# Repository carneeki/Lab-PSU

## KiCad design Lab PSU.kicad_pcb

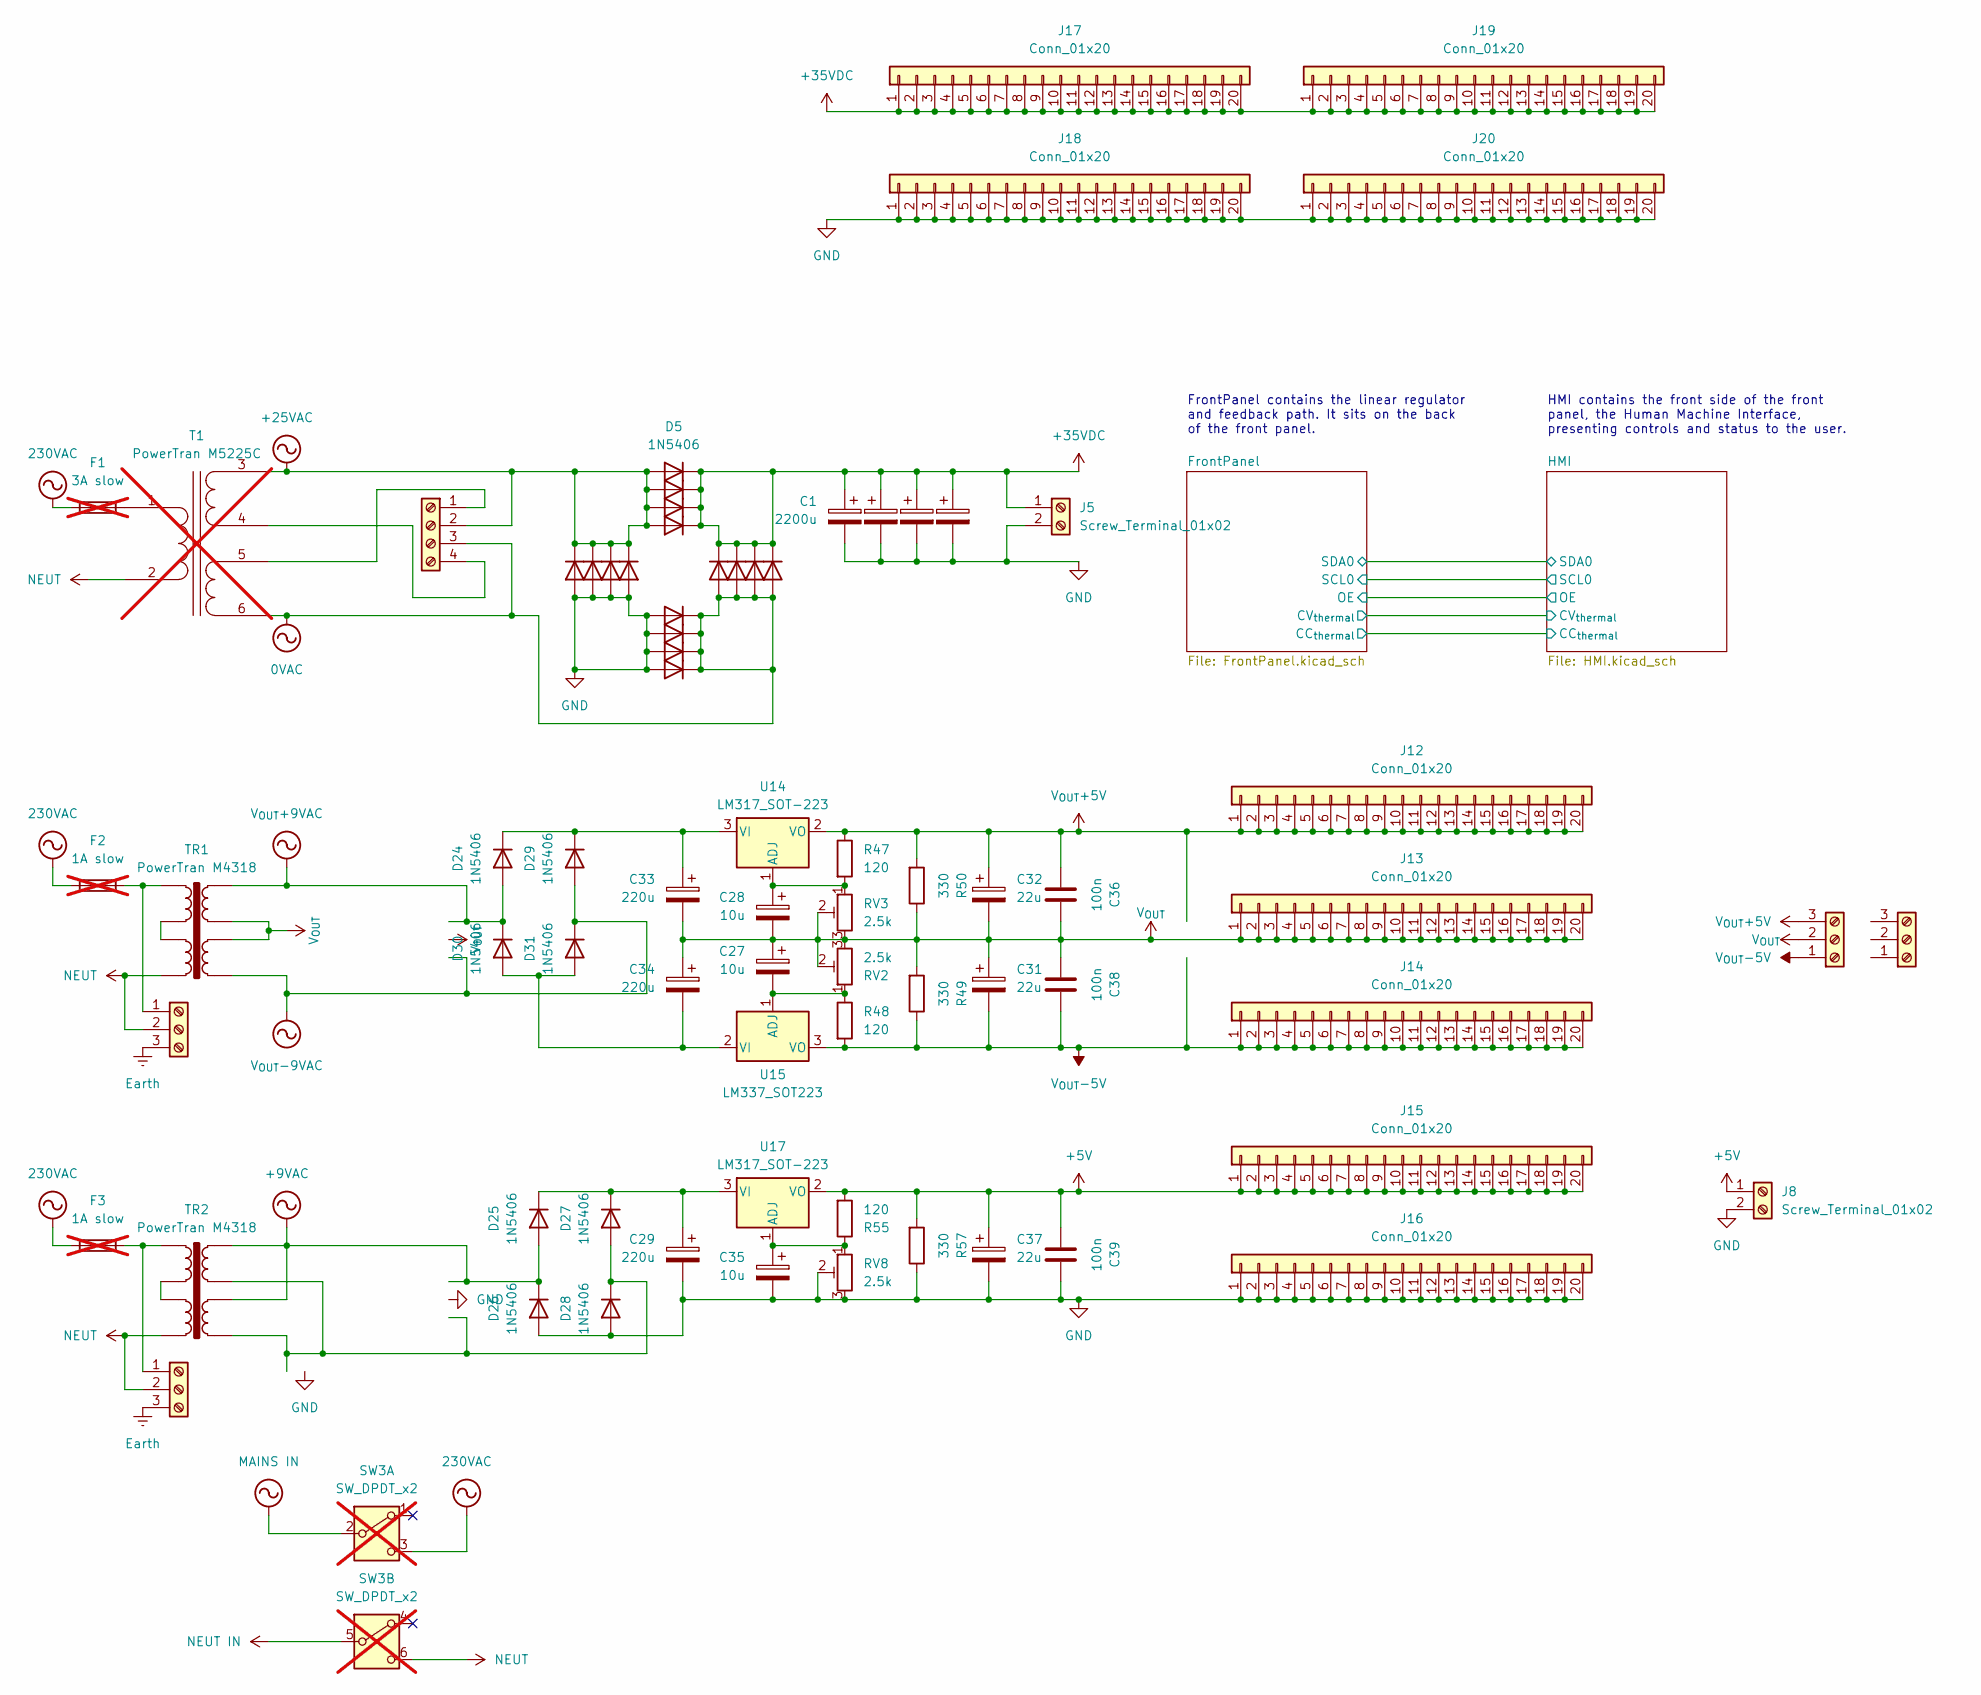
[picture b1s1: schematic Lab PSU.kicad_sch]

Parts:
C1, C2, C3, C4: 2200u; CP_Radial_D18.0mm_P7.50mm
C27, C28, C35: 10u; CP_Radial_D5.0mm_P2.00mm
C29, C33, C34: 220u; CP_Radial_D10.0mm_P5.00mm_P7.50mm
C31, C32, C37: 22u; CP_Radial_D6.3mm_P2.50mm
C36, C38, C39: 100n; C_1210_3225Metric_Pad1.33x2.70mm_HandSolder
D1, D2, D3, D4, D5, D6, D7, D8, D9, D10, D11, D12, D13, D14, D15, D16, D24, D25, D26, D27, D28, D29, D30, D31: 1N5406; D_DO-201AD_P15.24mm_Horizontal
F1: 3A slow; not fitted
F2, F3: 1A slow; not fitted
J1: Screw_Terminal_01x04; TerminalBlock_4Ucon_1x04_P3.50mm_Vertical
J4, J6, J7, J11: Screw_Terminal_01x03; TerminalBlock_4Ucon_1x03_P3.50mm_Vertical
J5, J8: Screw_Terminal_01x02; TerminalBlock_4Ucon_1x02_P3.50mm_Horizontal
J12, J13, J14, J15, J16, J17, J18: Conn_01x20; PinSocket_1x20_P2.54mm_Vertical
J19, J20: Conn_01x20; PinHeader_1x20_P2.54mm_Vertical
R47, R48, R55: 120; R_1210_3225Metric_Pad1.30x2.65mm_HandSolder
R49, R50, R57: 330; R_1210_3225Metric_Pad1.30x2.65mm_HandSolder
RV2, RV3, RV8: 2.5k; Potentiometer_Bourns_3299W_Vertical
SW3: SW_DPDT_x2; not fitted
T1: PowerTran M5225C; not fitted
TR1, TR2: PowerTran M4318; Transformer 53x53
U14, U17: LM317_SOT-223; SOT-223-3_TabPin2
U15: LM337_SOT223; SOT-223-3_TabPin2

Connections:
0VAC: D9.2 (A), D10.2 (A), D11.2 (A), D12.2 (A), D13.1 (K), D14.1 (K), D15.1 (K), D16.1 (K), J1.3, T1.6 (SD)
+5V: C37.1, C39.2, J8.1, J15.1, J15.2, J15.3, J15.4, J15.5, J15.6, J15.7, J15.8, J15.9, J15.10, J15.11, J15.12, J15.13, J15.14, J15.15, J15.16, J15.17, J15.18, J15.19, J15.20, R55.2, R57.2, U17.2 (VO); also elsewhere on the board
+9VAC: D25.2 (A), D26.1 (K), TR2.6, TR2.8
+25VAC: D1.1 (K), D2.1 (K), D3.1 (K), D4.1 (K), D5.2 (A), D6.2 (A), D7.2 (A), D8.2 (A), J1.2, T1.3 (SA)
+35VDC: C1.1, C2.1, C3.1, C4.1, D5.1 (K), D6.1 (K), D7.1 (K), D8.1 (K), D9.1 (K), D10.1 (K), D11.1 (K), D12.1 (K), J5.1, J17.1, J17.2, J17.3, J17.4, J17.5, J17.6, J17.7, J17.8, J17.9, J17.10, J17.11, J17.12, J17.13, J17.14, J17.15, J17.16, J17.17, J17.18, J17.19, J17.20, J19.1, J19.2, J19.3, J19.4, J19.5, J19.6, J19.7, J19.8, J19.9, J19.10, J19.11, J19.12, J19.13, J19.14, J19.15, J19.16, J19.17, J19.18, J19.19, J19.20; also elsewhere on the board
Earth: J6.3, J7.3
GND: C1.2, C2.2, C3.2, C4.2, C29.2, C35.2, C37.2, C39.1, D1.2 (A), D2.2 (A), D3.2 (A), D4.2 (A), D13.2 (A), D14.2 (A), D15.2 (A), D16.2 (A), D26.2 (A), D28.2 (A), J5.2, J8.2, J16.1, J16.2, J16.3, J16.4, J16.5, J16.6, J16.7, J16.8, J16.9, J16.10, J16.11, J16.12, J16.13, J16.14, J16.15, J16.16, J16.17, J16.18, J16.19, J16.20, J18.1, J18.2, J18.3, J18.4, J18.5, J18.6, J18.7, J18.8, J18.9, J18.10, J18.11, J18.12, J18.13, J18.14, J18.15, J18.16, J18.17, J18.18, J18.19, J18.20, J20.1, J20.2, J20.3, J20.4, J20.5, J20.6, J20.7, J20.8, J20.9, J20.10, J20.11, J20.12, J20.13, J20.14, J20.15, J20.16, J20.17, J20.18, J20.19, J20.20, R57.1, RV8.2, RV8.3; also elsewhere on the board
NEUT: J6.2, J7.2, SW3.6 (C), T1.2 (AB), TR1.4, TR2.4
unnamed: C33.1, D24.1 (K), D29.1 (K), U14.3 (VI)
unnamed: C29.1, D25.1 (K), D27.1 (K), U17.3 (VI)
unnamed: D27.2 (A), D28.1 (K), TR2.5, TR2.7
unnamed: C34.2, D30.2 (A), D31.2 (A), U15.2 (VI)
unnamed: F1.1, F2.1, F3.1, SW3.3 (C)
unnamed: F1.2, T1.1 (AA)
unnamed: J1.1, T1.5 (SC)
unnamed: J1.4, T1.4 (SB)
unnamed: F2.2, J6.1, TR1.1
unnamed: F3.2, J7.1, TR2.1
unnamed: TR1.2, TR1.3
unnamed: TR2.2, TR2.3
unnamed: C28.1, R47.2, RV3.1, U14.1 (ADJ)
unnamed: C27.2, R48.1, RV2.1, U15.1 (ADJ)
unnamed: C35.1, R55.1, RV8.1, U17.1 (ADJ)
V_{OUT}: C27.1, C28.2, C31.1, C32.2, C33.2, C34.1, C36.1, C38.1, J11.2, J13.1, J13.2, J13.3, J13.4, J13.5, J13.6, J13.7, J13.8, J13.9, J13.10, J13.11, J13.12, J13.13, J13.14, J13.15, J13.16, J13.17, J13.18, J13.19, J13.20, R49.2, R50.1, RV2.2, RV2.3, RV3.2, RV3.3, TR1.6, TR1.7; also elsewhere on the board
V_{OUT}+5V: C32.1, C36.2, J11.3, J12.1, J12.2, J12.3, J12.4, J12.5, J12.6, J12.7, J12.8, J12.9, J12.10, J12.11, J12.12, J12.13, J12.14, J12.15, J12.16, J12.17, J12.18, J12.19, J12.20, R47.1, R50.2, U14.2 (VO); also elsewhere on the board
V_{OUT}+9VAC: D24.2 (A), D30.1 (K), TR1.8
V_{OUT}-5V: C31.2, C38.2, J11.1, J14.1, J14.2, J14.3, J14.4, J14.5, J14.6, J14.7, J14.8, J14.9, J14.10, J14.11, J14.12, J14.13, J14.14, J14.15, J14.16, J14.17, J14.18, J14.19, J14.20, R48.2, R49.1, U15.3 (VO); also elsewhere on the board
V_{OUT}-9VAC: D29.2 (A), D31.1 (K), TR1.5

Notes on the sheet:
FrontPanel contains the linear regulator and feedback path. It sits on the back of the front panel.
HMI contains the front side of the front panel, the Human Machine Interface, presenting controls and status to the user.

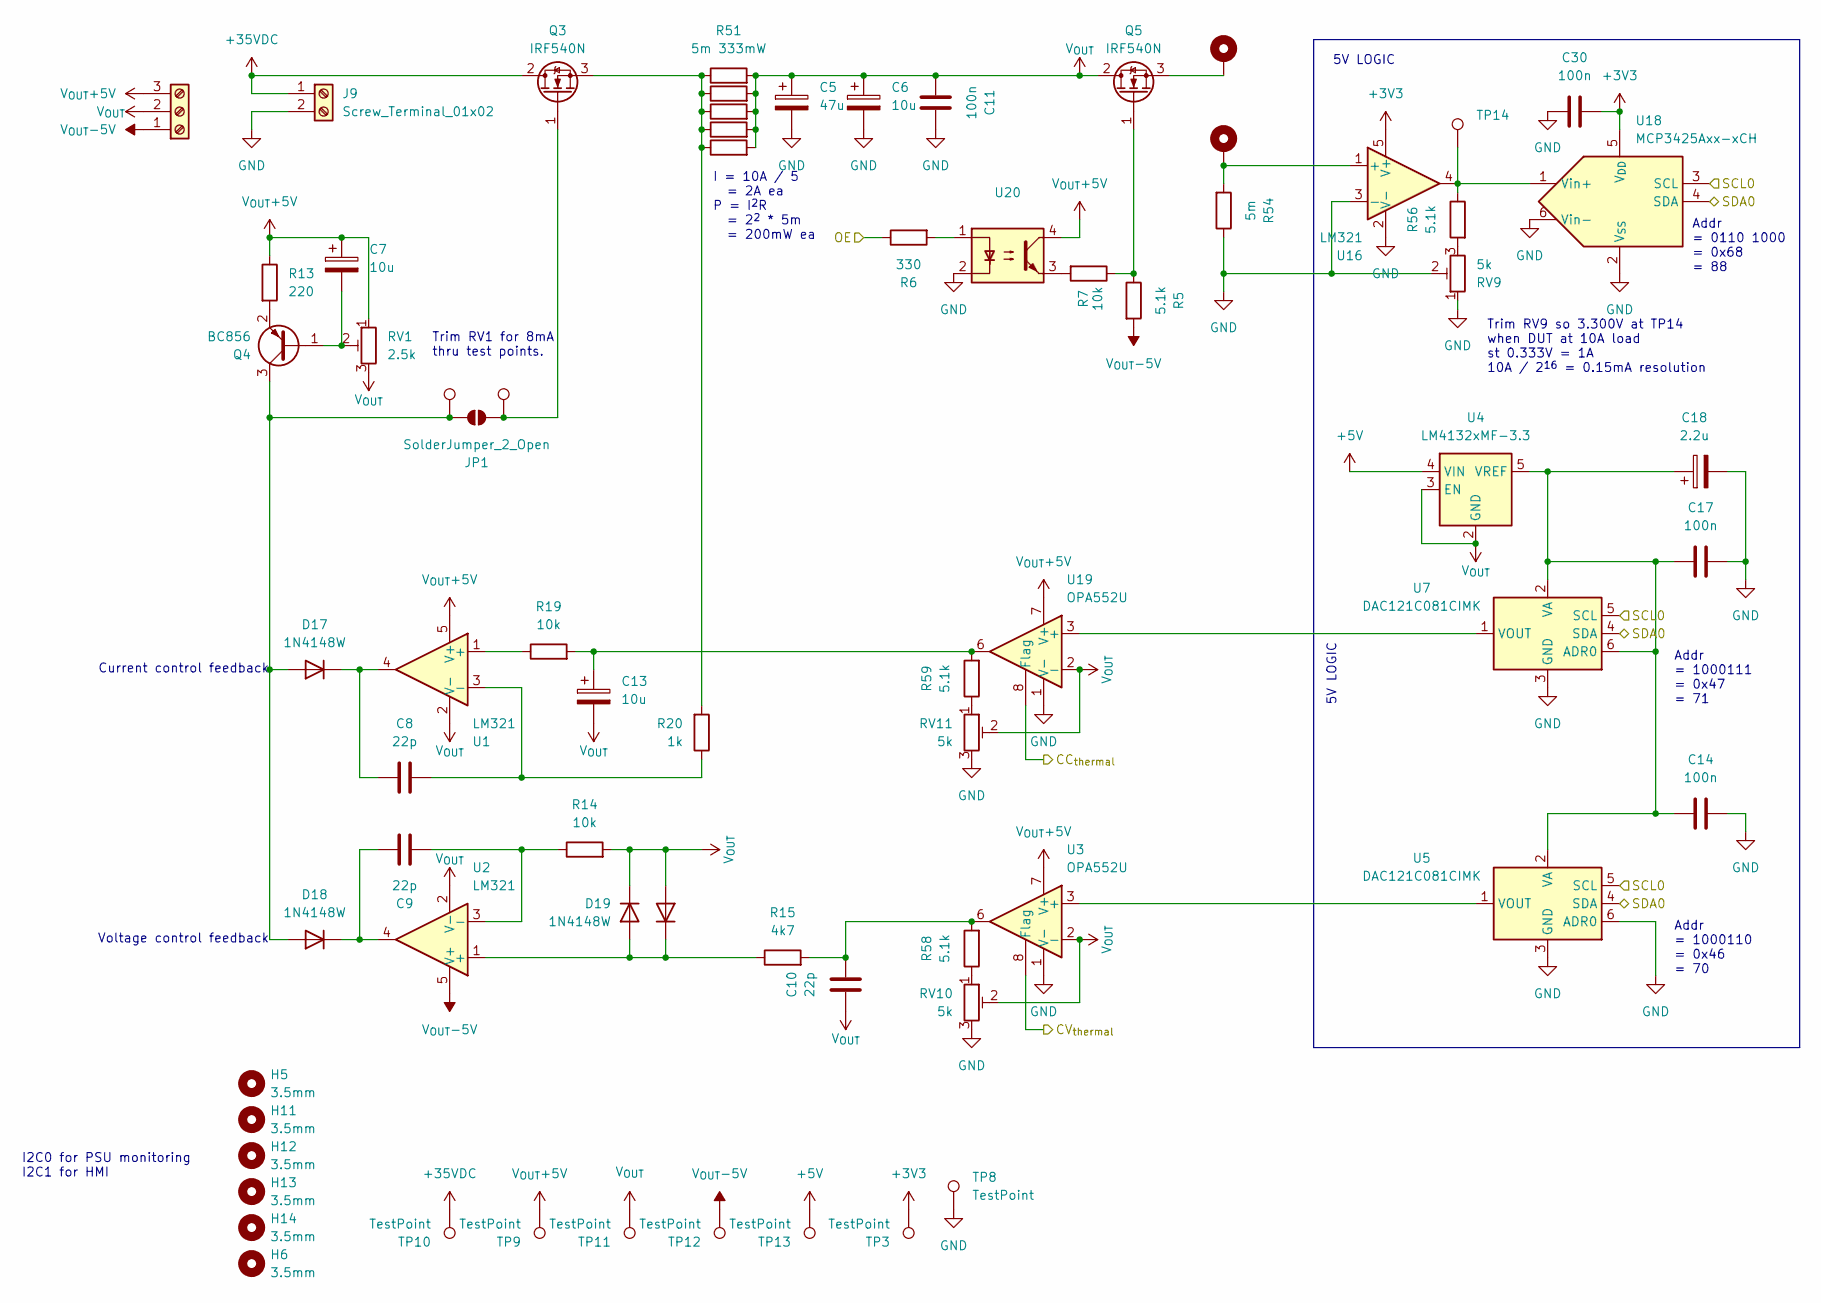
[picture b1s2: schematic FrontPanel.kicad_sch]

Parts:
C5: 47u; CP_Radial_D8.0mm_P3.50mm
C6, C7, C13: 10u; CP_Radial_D5.0mm_P2.00mm
C8, C9, C10: 22p; C_1210_3225Metric_Pad1.33x2.70mm_HandSolder
C11, C14, C17, C30: 100n; C_1210_3225Metric_Pad1.33x2.70mm_HandSolder
C18: 2.2u; CP_Radial_D5.0mm_P2.00mm
D17, D18, D19, D20: 1N4148W; D_SOD-123
H1, H2: MountingHole_Pad; MountingHole_4.3mm_M4_Pad_TopBottom
H5, H6, H11, H12, H13, H14: 3.5mm; MountingHole_3mm_Pad
J9: Screw_Terminal_01x02; TerminalBlock_4Ucon_1x02_P3.50mm_Horizontal
J10: Screw_Terminal_01x03; TerminalBlock_4Ucon_1x03_P3.50mm_Vertical
JP1: SolderJumper_2_Open; SolderJumper-2_P1.3mm_Open_TrianglePad1.0x1.5mm
Q3, Q5: IRF540N; TO-220-3_Vertical
Q4: BC856; SOT-23_Handsoldering
R1, R2, R3, R4, R54: 5m; R_0603_1608Metric_Pad0.98x0.95mm_HandSolder
R5, R56, R58, R59: 5.1k; R_1210_3225Metric_Pad1.30x2.65mm_HandSolder
R6: 330; R_1210_3225Metric_Pad1.30x2.65mm_HandSolder
R7, R14, R19: 10k; R_1210_3225Metric_Pad1.30x2.65mm_HandSolder
R13: 220; R_1210_3225Metric_Pad1.30x2.65mm_HandSolder
R15: 4k7; R_1210_3225Metric_Pad1.30x2.65mm_HandSolder
R20: 1k; R_1210_3225Metric_Pad1.30x2.65mm_HandSolder
R51: 5m 333mW; R_0603_1608Metric_Pad0.98x0.95mm_HandSolder
RV1: 2.5k; Potentiometer_Bourns_3299W_Vertical
RV9, RV10, RV11: 5k; Potentiometer_Bourns_3299W_Vertical
TP1, TP2: TestPoint; TestPoint_Keystone_5015_Micro_Mini
TP3, TP8, TP9, TP10, TP11, TP12, TP13, TP14: TestPoint; TestPoint_Keystone_5019_Miniature
U1, U2: LM321; SSOP-14_5.3x6.2mm_P0.65mm
U3, U19: OPA552U; SOIC-8_3.9x4.9mm_P1.27mm
U4: LM4132xMF-3.3; SOT-23-5
U5, U7: DAC121C081CIMK; SOT-23-6
U16: LM321; SOT-23-5_HandSoldering
U18: MCP3425Axx-xCH; SOT-23-6
U20: Optocoupler_DC_PhotoNPN_AKEC; DIP-4_W7.62mm_Socket_LongPads

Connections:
+3V3: C30.1, TP3.1 (1_1), U16.5 (V+), U18.5 (V_{DD}); also elsewhere on the board
+5V: TP13.1 (1_1), U4.4 (VIN); also elsewhere on the board
+35VDC: J9.1, Q3.2 (D), TP10.1 (1_1); also elsewhere on the board
/FrontPanel/CC_{thermal}: U19.8 (Flag); also elsewhere on the board
/FrontPanel/CV_{thermal}: U3.8 (Flag); also elsewhere on the board
/FrontPanel/OE: R6.1; also elsewhere on the board
/FrontPanel/SCL0: U5.5 (SCL), U7.5 (SCL), U18.3 (SCL); also elsewhere on the board
/FrontPanel/SDA0: U5.4 (SDA), U7.4 (SDA), U18.4 (SDA); also elsewhere on the board
GND: C5.2, C6.2, C11.2, C14.2, C17.2, C18.2, C30.2, J9.2, R54.1, RV9.1, RV9.2, RV10.3, RV11.3, TP8.1 (1_1), U3.1 (V-), U3.4 (V-), U3.5 (V-), U5.3 (GND), U5.6 (ADR0), U7.3 (GND), U16.2 (V-), U16.3 (-), U18.2 (V_{SS}), U18.6 (Vin-), U19.1 (V-), U19.4 (V-), U19.5 (V-), U20.2; also elsewhere on the board
unnamed: C10.2, R15.2, R58.2, U3.6
unnamed: C13.1, R19.2, R59.2, U19.6
unnamed: D17.2 (A), D18.2 (A), JP1.1 (A), Q4.3 (C), TP1.1 (1_1)
unnamed: C8.1, D17.1 (K), U1.4
unnamed: C9.1, D18.1 (K), U2.4
unnamed: D19.2 (A), D20.1 (K), R15.1, U2.1 (+)
unnamed: JP1.2 (B), Q3.1 (G), TP2.1 (1_1)
unnamed: Q3.3 (S), R1.1, R2.1, R3.1, R4.1, R20.2, R51.1
unnamed: C7.2, Q4.1 (B), RV1.2
unnamed: Q4.2 (E), R13.2
unnamed: Q5.1 (G), R5.1, R7.1
unnamed: H1.1 (1_1), Q5.3 (S)
unnamed: R6.2, U20.1
unnamed: R7.2, U20.3
unnamed: R56.2, RV9.3
unnamed: R58.1, RV10.1
unnamed: R59.1, RV11.1
unnamed: R19.1, U1.1 (+)
unnamed: C8.2, R20.1, U1.3 (-)
unnamed: C9.2, R14.1, U2.3 (-)
unnamed: U3.3 (+), U5.1 (VOUT)
unnamed: C14.1, C17.1, C18.1, U4.5 (VREF), U5.2 (VA), U7.2 (VA), U7.6 (ADR0)
unnamed: H2.1 (1_1), R54.2, U16.1 (+)
unnamed: R56.1, TP14.1 (1_1), U16.4, U18.1 (Vin+)
unnamed: U7.1 (VOUT), U19.3 (+)
V_{OUT}: C5.1, C6.1, C10.1, C11.1, C13.2, D19.1 (K), D20.2 (A), J10.2, Q5.2 (D), R1.2, R2.2, R3.2, R4.2, R14.2, R51.2, RV1.3, RV10.2, RV11.2, TP11.1 (1_1), U1.2 (V-), U2.2 (V-), U3.2 (-), U4.2 (GND), U4.3 (EN), U19.2 (-); also elsewhere on the board
V_{OUT}+5V: C7.1, J10.3, R13.1, RV1.1, TP9.1 (1_1), U1.5 (V+), U3.7 (V+), U19.7 (V+), U20.4; also elsewhere on the board
V_{OUT}-5V: J10.1, R5.2, TP12.1 (1_1), U2.5 (V+); also elsewhere on the board

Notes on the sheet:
I2C0 for PSU monitoring I2C1 for HMI
Addr = 1000110 = 0x46 = 70
I = 10A / 5 = 2A ea P = I^{2}R = 2^{2} * 5m = 200mW ea
Trim RV1 for 8mA thru test points.
Trim RV9 so 3.300V at TP14 when DUT at 10A load st 0.333V = 1A 10A / 2^{16} = 0.15mA resolution
Voltage control feedback
Addr = 0110 1000 = 0x68 = 88
Current control feedback
5V LOGIC
Addr = 1000111 = 0x47 = 71

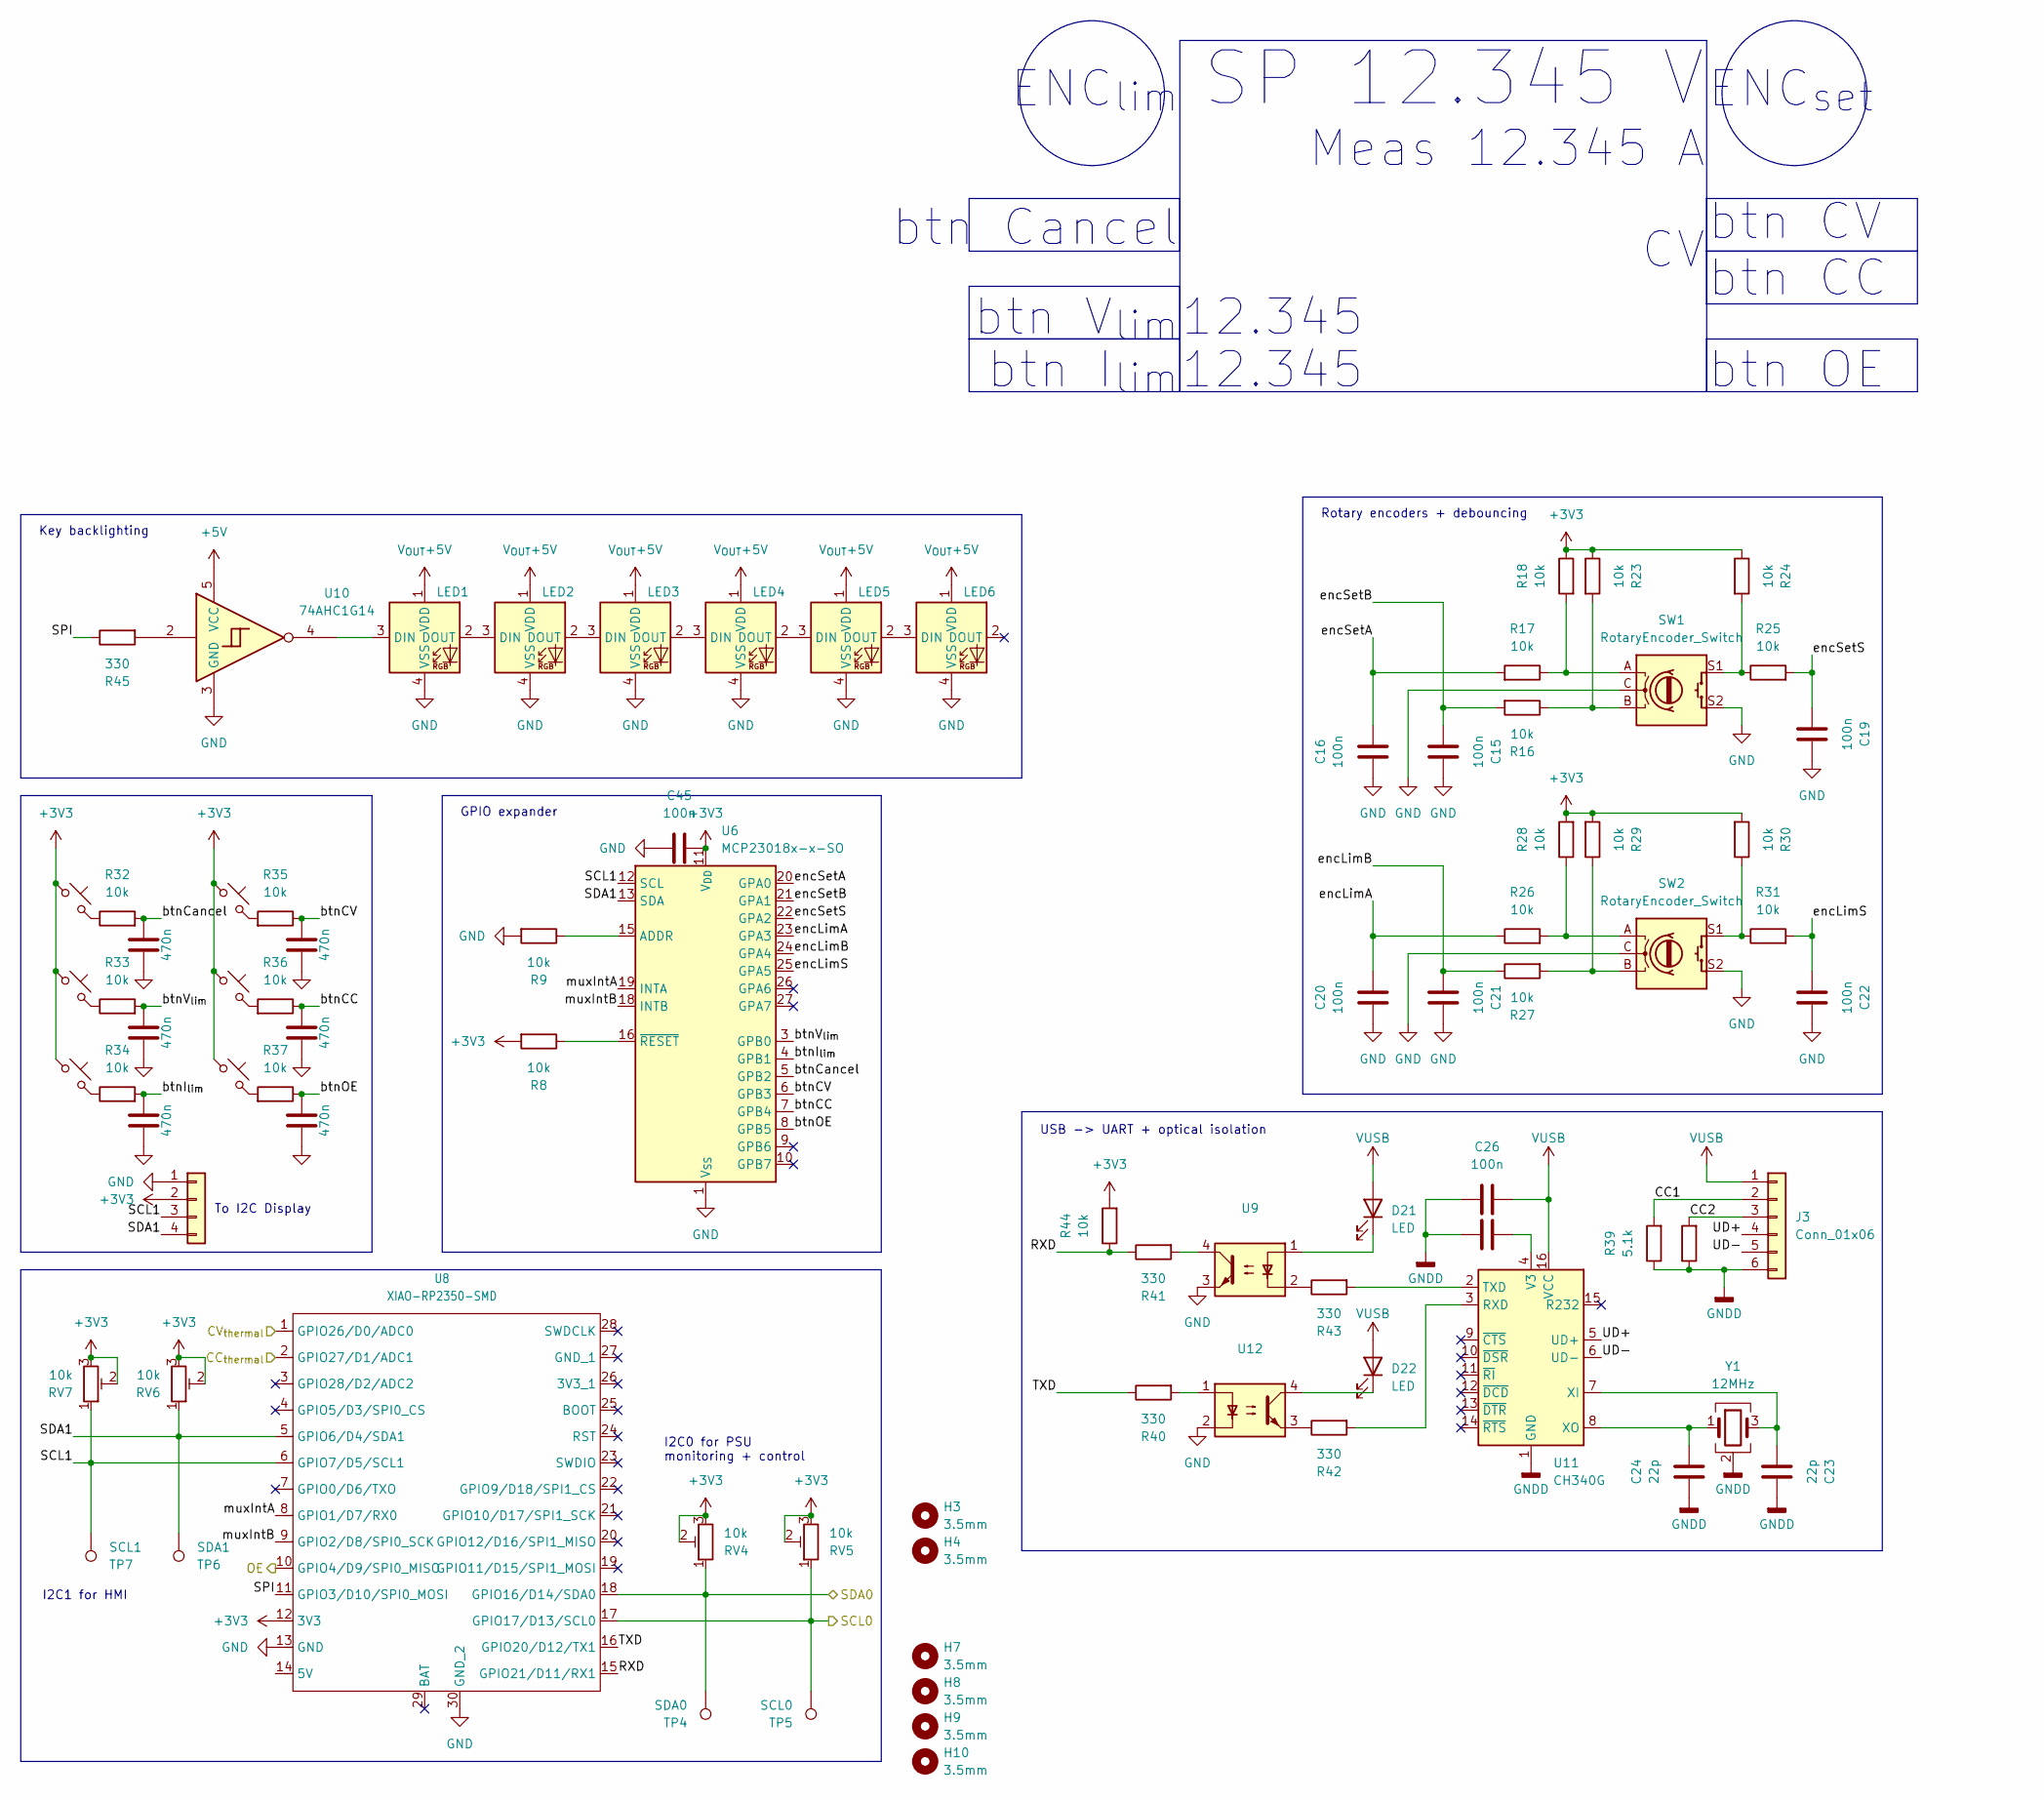
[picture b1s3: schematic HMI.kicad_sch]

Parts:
C12, C40, C41, C42, C43, C44: 470n; C_1210_3225Metric_Pad1.33x2.70mm_HandSolder
C15, C16, C19, C20, C21, C22, C25, C26, C45: 100n; C_1210_3225Metric_Pad1.33x2.70mm_HandSolder
C23, C24: 22p; C_1210_3225Metric_Pad1.33x2.70mm_HandSolder
D21, D22: LED; LED_1210_3225Metric_Pad1.42x2.65mm_HandSolder
H3, H4, H7, H8, H9, H10: 3.5mm; MountingHole_3mm_Pad
J2: Conn_01x04; I2C OLED
J3: Conn_01x06; JST_PH_B6B-PH-K_1x06_P2.00mm_Vertical
LED1, LED2, LED3, LED4, LED5, LED6: SK6812MINI-E; LED_MX_6028R
MX1, MX2, MX3, MX4, MX5, MX6: MX_SW_solder; SW_MX_1u
R8, R9, R16, R17, R18, R23, R24, R25, R26, R27, R28, R29, R30, R31, R32, R33, R34, R35, R36, R37, R44: 10k; R_1210_3225Metric_Pad1.30x2.65mm_HandSolder
R38, R39: 5.1k; R_1210_3225Metric_Pad1.30x2.65mm_HandSolder
R40, R41, R42, R43, R45: 330; R_1210_3225Metric_Pad1.30x2.65mm_HandSolder
RV4, RV5, RV6, RV7: 10k; Potentiometer_Bourns_3299W_Vertical
SW1, SW2: RotaryEncoder_Switch; RotaryEncoder_Alps_EC11E-Switch_Vertical_H20mm
TP4: SDA0; TestPoint_Keystone_5019_Miniature
TP5: SCL0; TestPoint_Keystone_5019_Miniature
TP6: SDA1; TestPoint_Keystone_5019_Miniature
TP7: SCL1; TestPoint_Keystone_5019_Miniature
U6: MCP23018x-x-SO; SOIC-28W_7.5x17.9mm_P1.27mm
U8: XIAO-RP2350-SMD; XIAO-RP2350-DIP
U9, U12: Optocoupler_DC_PhotoNPN_AKEC; DIP-4_W7.62mm_Socket_LongPads
U10: 74AHC1G14
U11: CH340G; SOIC-16_3.9x9.9mm_P1.27mm
Y1: 12MHz; Crystal_SMD_3225-4Pin_3.2x2.5mm

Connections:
+3V3: C45.2, J2.2, MX1.1, MX2.1, MX3.1, MX4.1, MX5.1, MX6.1, R8.2, R18.1, R23.1, R24.1, R28.2, R29.2, R30.2, R44.2, RV4.2, RV4.3, RV5.2, RV5.3, RV6.2, RV6.3, RV7.2, RV7.3, U6.11 (V_{DD}), U8.12 (3V3); also elsewhere on the board
/FrontPanel/CC_{thermal}: U8.2 (GPIO27/D1/ADC1); also elsewhere on the board
/FrontPanel/CV_{thermal}: U8.1 (GPIO26/D0/ADC0); also elsewhere on the board
/FrontPanel/OE: U8.10 (GPIO4/D9/SPI0_MISO); also elsewhere on the board
/FrontPanel/SCL0: RV5.1, TP5.1 (1_1), U8.17 (GPIO17/D13/SCL0); also elsewhere on the board
/FrontPanel/SDA0: RV4.1, TP4.1 (1_1), U8.18 (GPIO16/D14/SDA0); also elsewhere on the board
/HMI/CC1: J3.2, R39.2
/HMI/CC2: J3.3, R38.2
/HMI/RXD: R41.1, R44.1, U8.15 (GPIO21/D11/RX1)
/HMI/SCL1: J2.3, RV7.1, TP7.1 (1_1), U6.12 (SCL), U8.6 (GPIO7/D5/SCL1)
/HMI/SDA1: J2.4, RV6.1, TP6.1 (1_1), U6.13 (SDA), U8.5 (GPIO6/D4/SDA1)
/HMI/SPI: R45.1, U8.11 (GPIO3/D10/SPI0_MOSI)
/HMI/TXD: R40.1, U8.16 (GPIO20/D12/TX1)
/HMI/UD+: J3.4, U11.5 (UD+)
/HMI/UD-: J3.5, U11.6 (UD-)
/HMI/btnCC: C41.1, R36.1, U6.7 (GPB4)
/HMI/btnCV: C12.1, R35.1, U6.6 (GPB3)
/HMI/btnCancel: C42.2, R32.2, U6.5 (GPB2)
/HMI/btnI_{lim}: C43.2, R34.2, U6.4 (GPB1)
/HMI/btnOE: C44.1, R37.1, U6.8 (GPB5)
/HMI/btnV_{lim}: C40.2, R33.2, U6.3 (GPB0)
/HMI/encLimA: C20.1, R26.1, U6.23 (GPA3)
/HMI/encLimB: C21.1, R27.1, U6.24 (GPA4)
/HMI/encLimS: C22.1, R31.2, U6.25 (GPA5)
/HMI/encSetA: C16.2, R17.2, U6.20 (GPA0)
/HMI/encSetB: C15.2, R16.2, U6.21 (GPA1)
/HMI/encSetS: C19.2, R25.2, U6.22 (GPA2)
/HMI/muxIntA: U6.19 (INTA), U8.8 (GPIO1/D7/RX0)
/HMI/muxIntB: U6.18 (INTB), U8.9 (GPIO2/D8/SPI0_SCK)
GND: C12.2, C15.1, C16.1, C19.1, C20.2, C21.2, C22.2, C40.1, C41.2, C42.1, C43.1, C44.2, C45.1, J2.1, LED1.4 (VSS), LED2.4 (VSS), LED3.4 (VSS), LED4.4 (VSS), LED5.4 (VSS), LED6.4 (VSS), R9.2, SW1.C, SW1.S2, SW2.C, SW2.S2, U6.1 (V_{SS}), U8.13 (GND), U8.30 (GND_2), U9.3, U10.3 (GND), U12.2; also elsewhere on the board
GNDD: C23.1, C24.1, C25.2, C26.2, J3.6, R38.1, R39.1, U11.1 (GND), Y1.2 (G), Y1.4 (G)
unnamed: D21.1 (K), U9.1
unnamed: D22.1 (K), U12.4
unnamed: LED1.3 (DIN), U10.4
unnamed: LED1.2 (DOUT), LED2.3 (DIN)
unnamed: LED2.2 (DOUT), LED3.3 (DIN)
unnamed: LED3.2 (DOUT), LED4.3 (DIN)
unnamed: LED4.2 (DOUT), LED5.3 (DIN)
unnamed: LED5.2 (DOUT), LED6.3 (DIN)
unnamed: MX1.2, R32.1
unnamed: MX2.2, R33.1
unnamed: MX3.2, R34.1
unnamed: MX4.2, R35.2
unnamed: MX5.2, R36.2
unnamed: MX6.2, R37.2
unnamed: R16.1, R23.2, SW1.B
unnamed: R17.1, R18.2, SW1.A
unnamed: R24.2, R25.1, SW1.S1
unnamed: R26.2, R28.1, SW2.A
unnamed: R27.2, R29.1, SW2.B
unnamed: R30.1, R31.1, SW2.S1
unnamed: R40.2, U12.1
unnamed: R41.2, U9.4
unnamed: R42.1, U12.3
unnamed: R43.1, U9.2
unnamed: R45.2, U10.2
unnamed: R9.1, U6.15 (ADDR)
unnamed: R8.1, U6.16 (~RESET)
unnamed: R42.2, U11.3 (RXD)
unnamed: R43.2, U11.2 (TXD)
unnamed: C25.1, U11.4 (V3)
unnamed: C23.2, U11.7 (XI), Y1.3
unnamed: C24.2, U11.8 (XO), Y1.1
VUSB: C26.1, D21.2 (A), D22.2 (A), J3.1, U11.16 (VCC)
V_{OUT}+5V: LED1.1 (VDD), LED2.1 (VDD), LED3.1 (VDD), LED4.1 (VDD), LED5.1 (VDD), LED6.1 (VDD); also elsewhere on the board

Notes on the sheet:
Meas 12.345 A
Rotary encoders + debouncing
USB -> UART + optical isolation
btn CV btn CC
ENC_{set}
To I2C Display
I2C0 for PSU monitoring + control
12.345
btn Cancel
btn I_{lim}
I2C1 for HMI
ENC_{lim}
btn V_{lim}
SP 12.345 V
Key backlighting
GPIO expander
btn OE

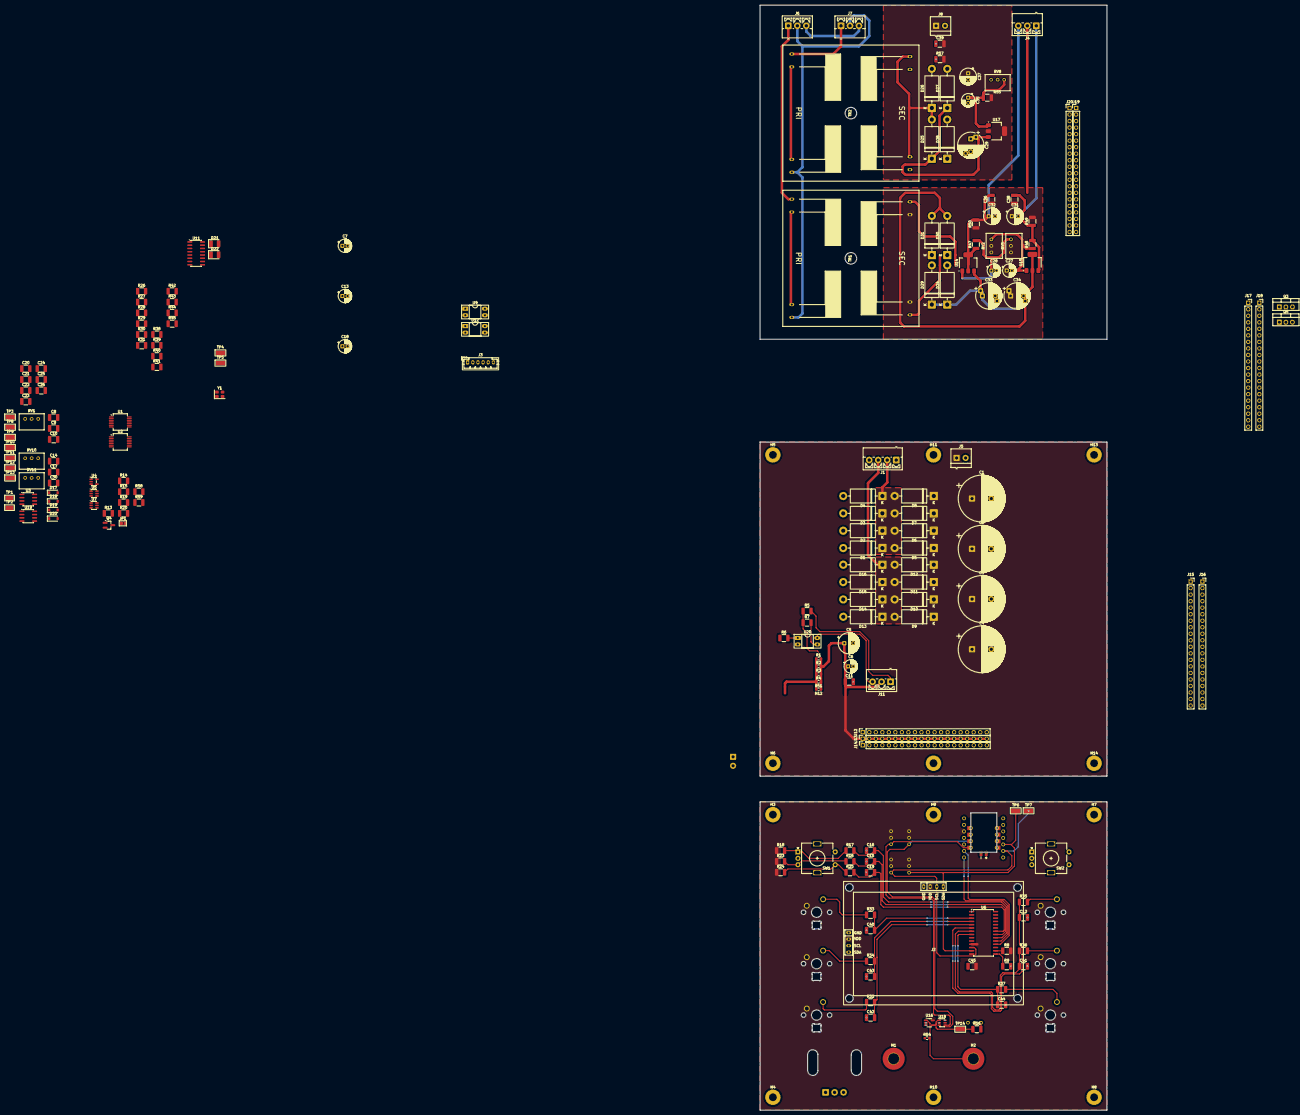
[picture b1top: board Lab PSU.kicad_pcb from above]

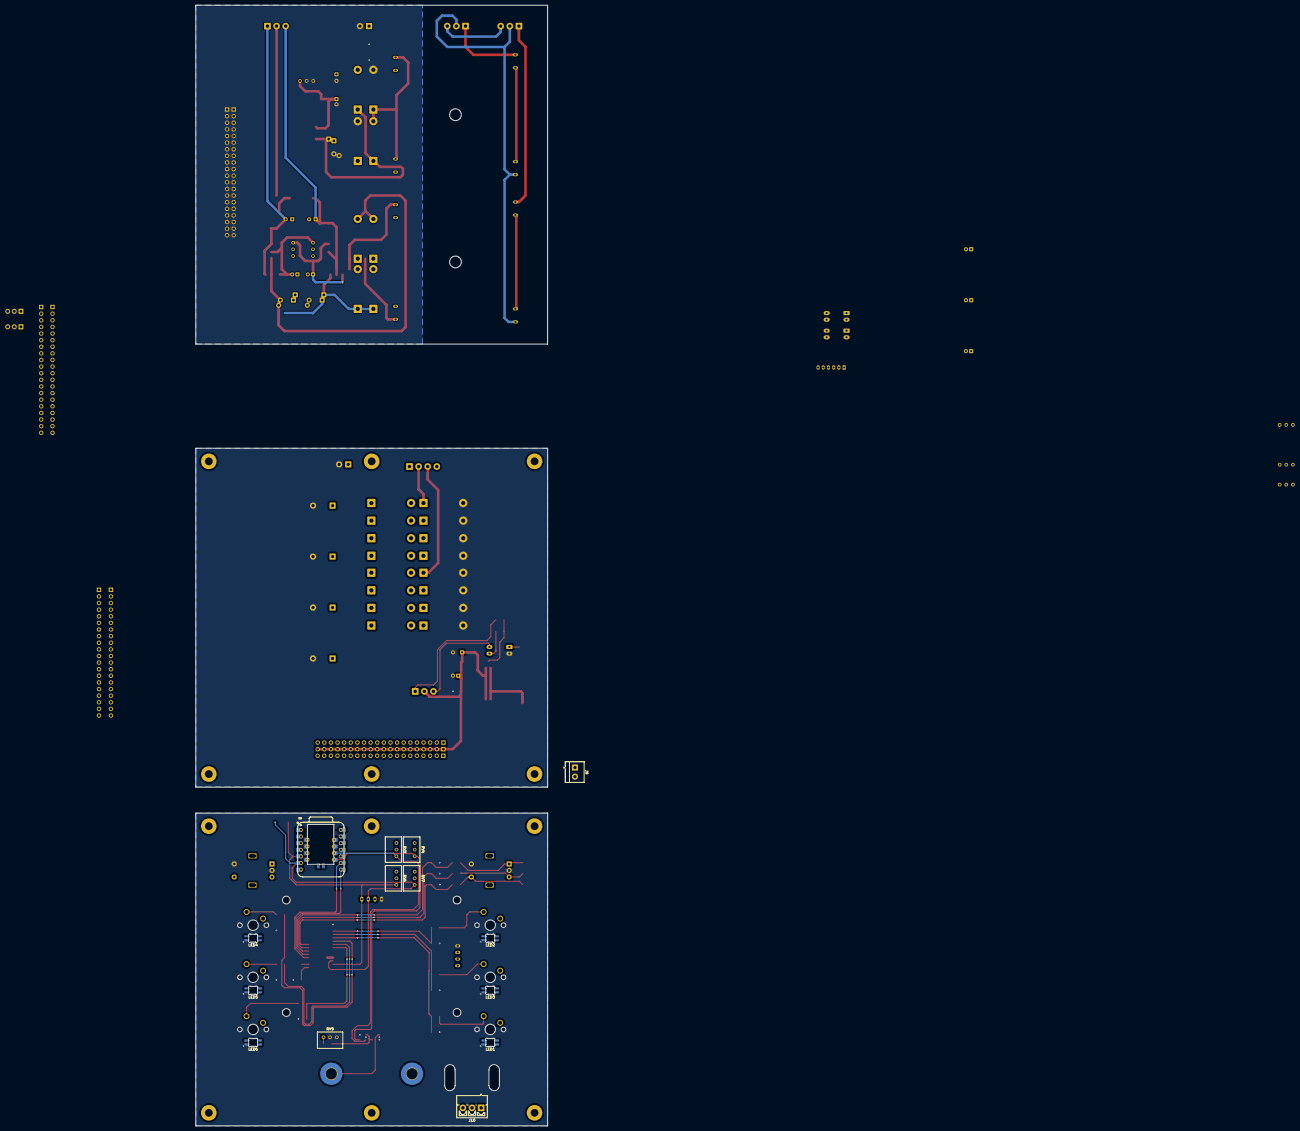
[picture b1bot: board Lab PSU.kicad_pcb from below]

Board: 2 copper layers, 135.0 x 430.0 mm, 224 parts (14 on the bottom side), 110 nets.

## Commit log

2026-03-12 initial import
2026-03-15 many changes
2026-03-16 do some work on the regulator boards
2026-03-16 shrink regulator board a little
2026-03-22 kicad v10. many changes to invididual boards
2026-03-27 interim commit
2026-03-27 add .history to .gitignore
